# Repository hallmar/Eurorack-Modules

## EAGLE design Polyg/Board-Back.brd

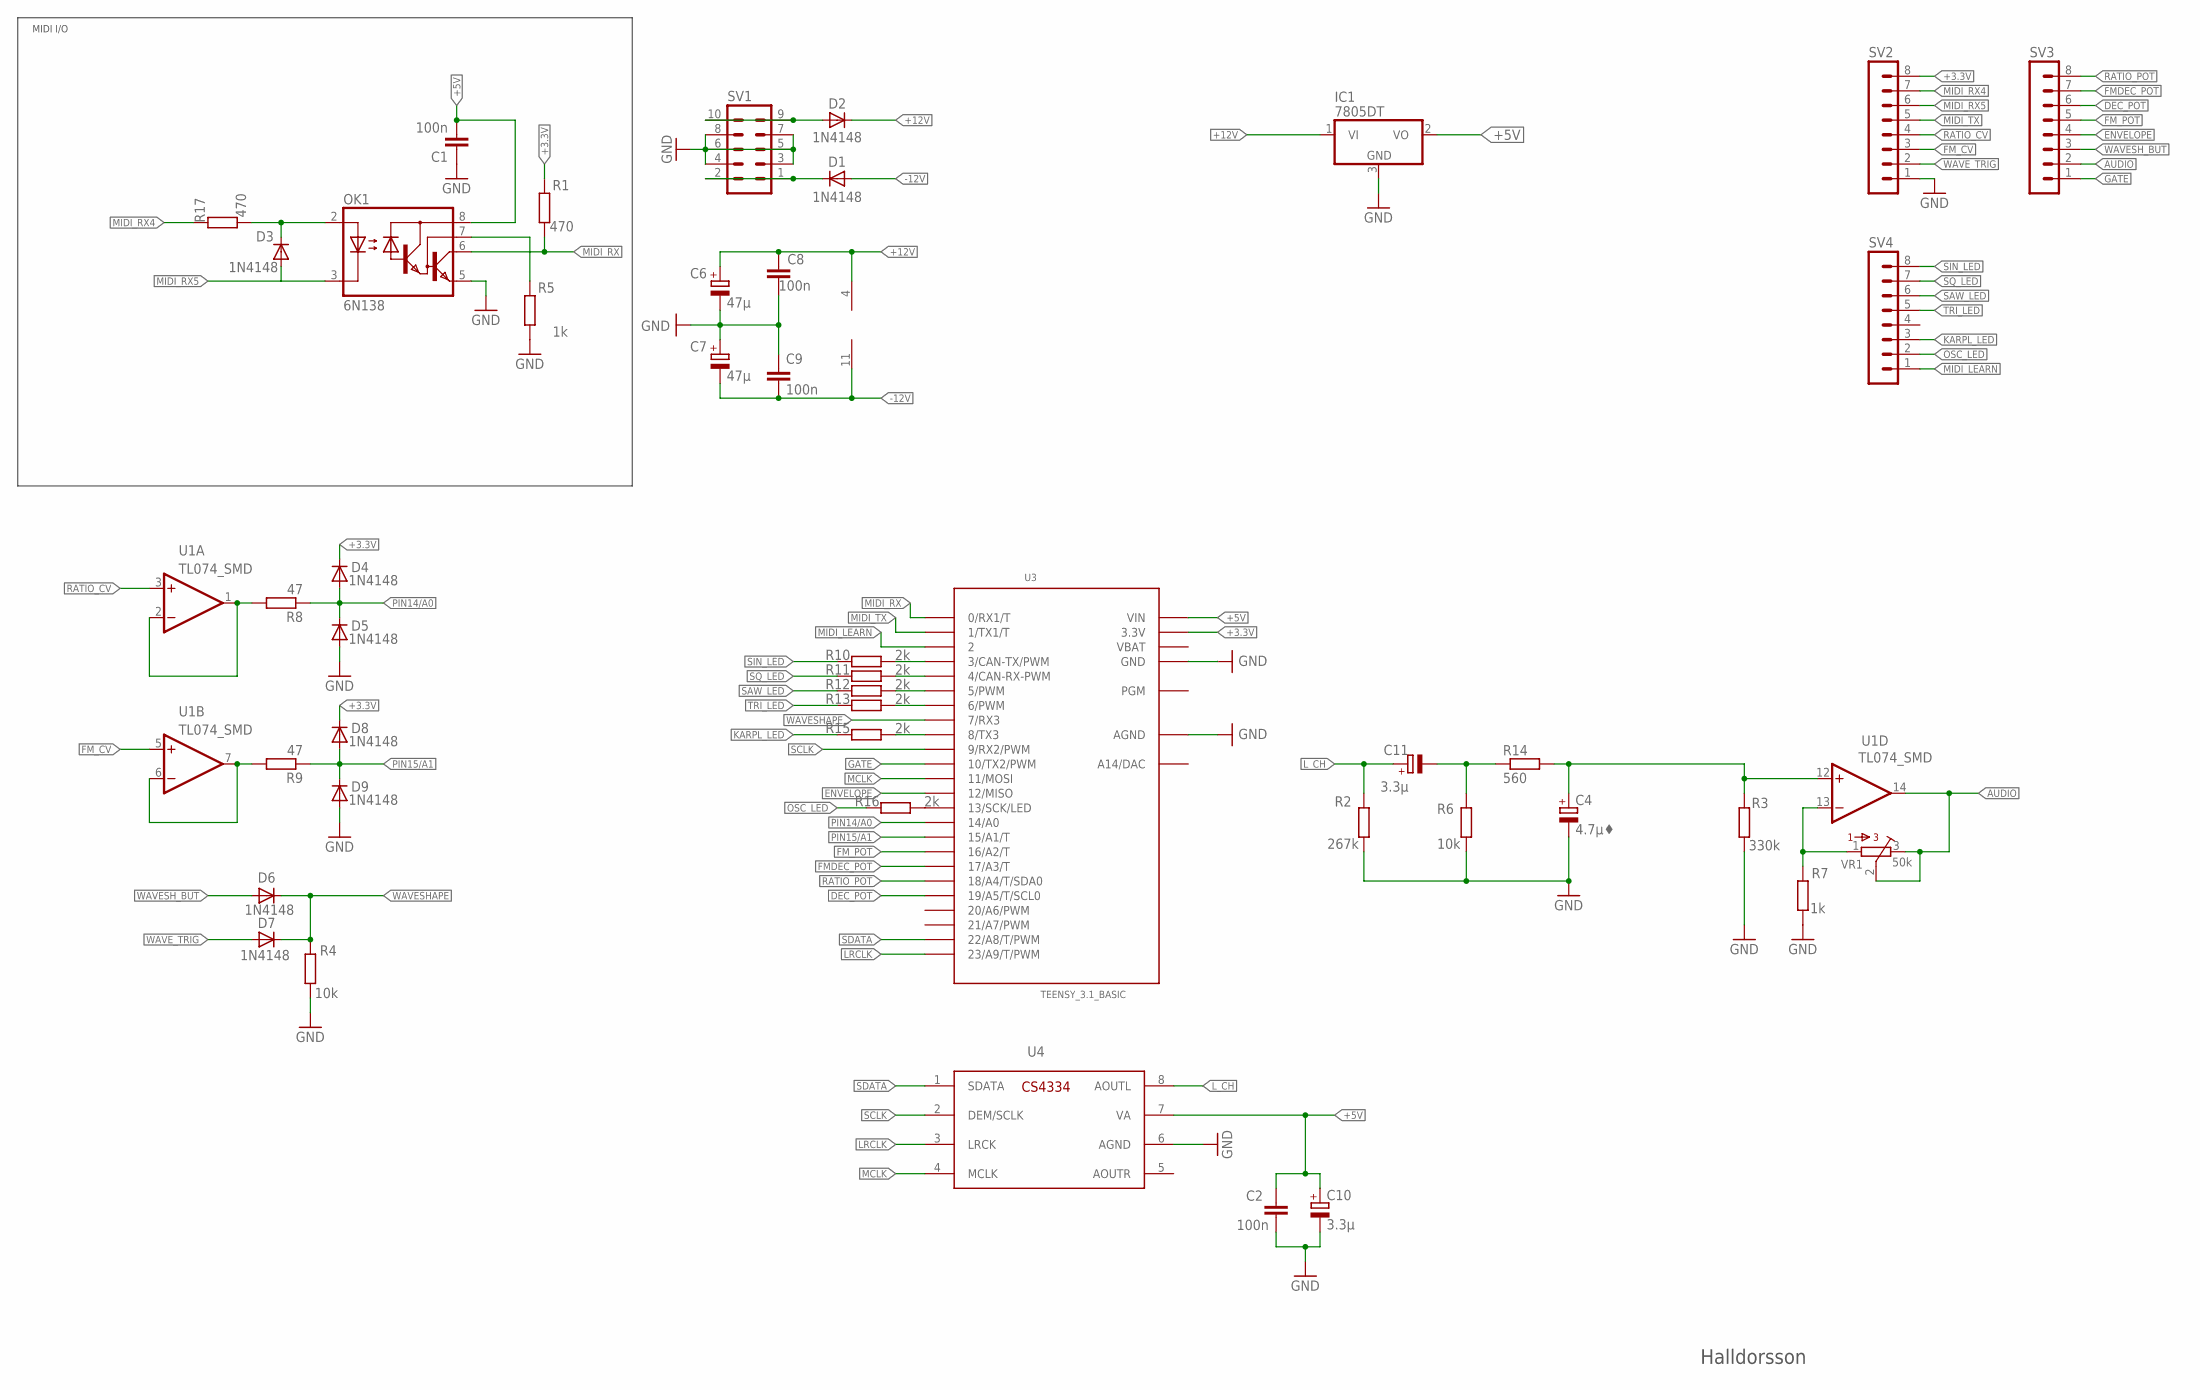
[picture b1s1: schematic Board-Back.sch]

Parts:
C1, C2, C8, C9: 100n; C1206
C4: 4.7µ♦; 153CLV-0405
C6, C7: 47µ; E5-6
C10: 3.3µ; 153CLV-0505
C11: 3.3µ; 153CLV-0405
D1, D2, D3, D4, D5, D6, D7, D8, D9: 1N4148; DO35-7
IC1: 7805DT; TO252
OK1: 6N138; DIL08
R1, R17: 470; M1206
R2: 267k; M1206
R3: 330k; M1206
R4, R6: 10k; M1206
R5, R7: 1k; M1206
R8, R9: 47; M1206
R10, R11, R12, R13, R15, R16: 2k; M1206
R14: 560; M1206
SV1: 10PIN_BACKSIDE
SV2, SV3, SV4: MA08-1
U1: TL074_SMD; SO14
U3: TEENSY_3.1_BASIC
U4: CS4334; SOIC127P600X175-8N
VR1: 50k; BOURNS_3362P_TRIMMER

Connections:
+3.3V: D4.C, D8.C, R1.2, SV2.8, U3.3.3V, U3.3.3V1 (3.3V)
+5V: C1.2, C2.1, C10.+, IC1.2 (VO), OK1.8 (VCC), U3.VIN, U4.7 (VA)
+12V: C6.+, C8.1, D2.C, IC1.1 (VI), U1.4 (V+)
-12V: C7.-, C9.2, D1.A, U1.11 (V-)
AUDIO: SV3.2, U1.14 (OUT), VR1.2, VR1.3
DEC_POT: SV3.6, U3.19/A5 (19/A5/T/SCL0)
ENVELOPE: SV3.4, U3.12 (12/MISO)
FMDEC_POT: SV3.7, U3.17/A3 (17/A3/T)
FM_CV: SV2.3, U1.5 (+IN)
FM_POT: SV3.5, U3.16/A2 (16/A2/T)
GATE: SV3.1, U3.10 (10/TX2/PWM)
GND: C1.1, C2.2, C4.-, C6.-, C7.+, C8.2, C9.1, C10.-, D5.A, D9.A, IC1.3 (GND), OK1.5 (GND), R2.2, R3.2, R4.1, R5.1, R6.2, R7.2, SV1.3, SV1.4, SV1.5, SV1.6, SV1.7, SV1.8, SV2.1, U3.AGND, U3.GND, U3.GND1 (GND), U4.6 (AGND)
KARPL_LED: R15.2, SV4.3
LRCLK: U3.23/A9 (23/A9/T/PWM), U4.3 (LRCK)
L_CH: C11.+, R2.1, U4.8 (AOUTL)
MCLK: U3.11 (11/MOSI), U4.4 (MCLK)
MIDI_LEARN: SV4.1, U3.2
MIDI_RX: OK1.6 (VO), R1.1, U3.0 (0/RX1/T)
MIDI_RX4: R17.2, SV2.7
MIDI_RX5: D3.A, OK1.3 (C), SV2.6
MIDI_TX: SV2.5, U3.1 (1/TX1/T)
unnamed: C11.-, R6.1, R14.1
unnamed: D1.C, SV1.1, SV1.2
unnamed: D3.C, OK1.2 (A), R17.1
unnamed: OK1.7 (VB), R5.2
unnamed: R7.1, U1.13 (-IN), VR1.1
unnamed: D2.A, SV1.9, SV1.10
unnamed: R16.1, U3.13 (13/SCK/LED)
unnamed: C4.+, R3.1, R14.2, U1.12 (+IN)
unnamed: R10.1, U3.3 (3/CAN-TX/PWM)
unnamed: R11.1, U3.4 (4/CAN-RX-PWM)
unnamed: R12.1, U3.5 (5/PWM)
unnamed: R9.2, U1.6 (-IN), U1.7 (OUT)
unnamed: R8.2, U1.1 (OUT), U1.2 (-IN)
unnamed: R13.1, U3.6 (6/PWM)
unnamed: R15.1, U3.8 (8/TX3)
OSC_LED: R16.2, SV4.2
PIN14/A0: D4.A, D5.C, R8.1, U3.14/A0
PIN15/A1: D8.A, D9.C, R9.1, U3.15/A1 (15/A1/T)
RATIO_CV: SV2.4, U1.3 (+IN)
RATIO_POT: SV3.8, U3.18/A4 (18/A4/T/SDA0)
SAW_LED: R12.2, SV4.6
SCLK: U3.9 (9/RX2/PWM), U4.2 (DEM/SCLK)
SDATA: U3.22/A8 (22/A8/T/PWM), U4.1 (SDATA)
SIN_LED: R10.2, SV4.8
SQ_LED: R11.2, SV4.7
TRI_LED: R13.2, SV4.5
VBAT: U3.VBAT
WAVESHAPE: D6.C, D7.C, R4.2, U3.7 (7/RX3)
WAVESH_BUT: D6.A, SV3.3
WAVE_TRIG: D7.A, SV2.2

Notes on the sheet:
MIDI I/O
Halldorsson

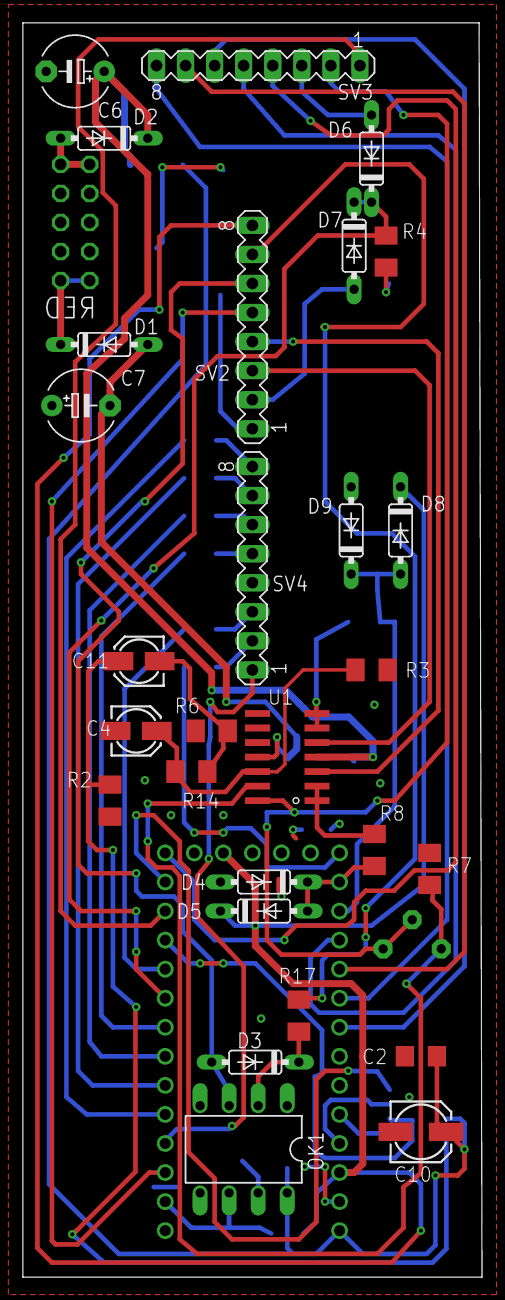
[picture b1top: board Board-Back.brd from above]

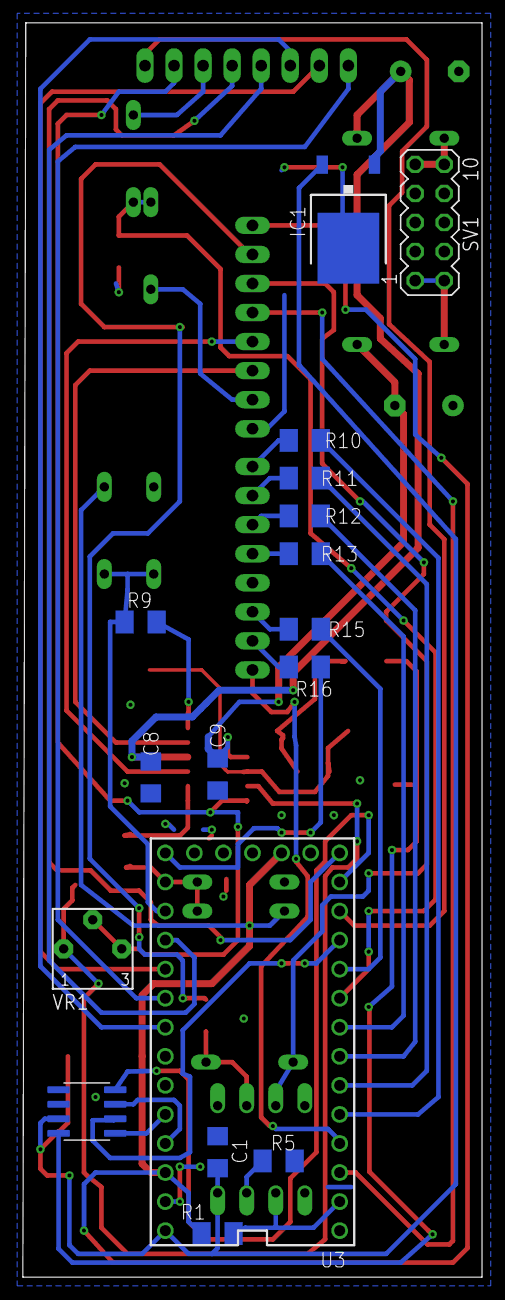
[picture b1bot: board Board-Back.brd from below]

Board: 2 copper layers, 40.1 x 109.7 mm, 45 parts (16 on the bottom side), 50 nets.
